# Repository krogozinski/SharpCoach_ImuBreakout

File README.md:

# SharpCoach IMU Breakout
A simple breakout board for the ST LSM6DS33 IMU using a modified Digilent Type 2A PMOD interface. The board breaks out both interrupt pins to facilitate notifying the controlling device of IMU events.

# Pinout
1. SS
2. MOSI
3. MISO
4. SCK
5. GND
6. VCC
7. INT1
8. NC
9. INT2
10. NC
11. GND
12. VCC

# License

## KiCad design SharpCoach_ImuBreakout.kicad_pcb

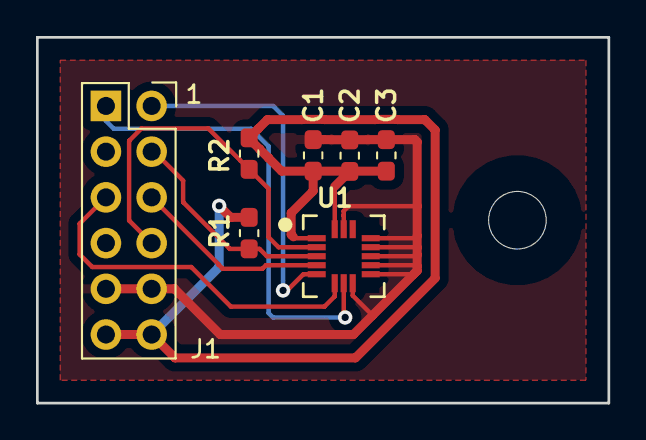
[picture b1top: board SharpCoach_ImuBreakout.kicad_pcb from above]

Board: 2 copper layers, 31.8 x 20.3 mm, 7 parts (0 on the bottom side), 8 nets.

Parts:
C1, C2: 100n; C_0603_1608Metric_Pad1.05x0.95mm_HandSolder
C3: 1u; C_0603_1608Metric_Pad1.05x0.95mm_HandSolder
J1: PMOD_Type2A_Variant01; PMOD_SpecB
R1, R2: 10k; R_0603_1608Metric_Pad1.05x0.95mm_HandSolder
U1: LSM6DS33

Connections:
+3V3: C1.1, C2.1, C3.1, J1.6, J1.12, R1.1, R2.1, U1.1, U1.16
/INT1: J1.7, U1.7
/INT2: J1.9, U1.6
/MISO: J1.3, U1.4
/MOSI: J1.2, R1.2, U1.3
/SCK: J1.4, R2.2, U1.2
/SS: J1.1, U1.5
GND: C1.2, C2.2, C3.2, J1.5, J1.11, U1.8, U1.9, U1.10, U1.11, U1.12, U1.13, U1.15

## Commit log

2018-08-01 Initial commit of schematics
2018-08-01 Started PCB layout.
2018-08-01 Started PCB trace routing
2018-08-02 Finished PCB trace routing.
2018-08-02 Added copper pour and board outline to PCB layout.
2018-08-02 Updated mask expansion to Oshpark recommended value of 2mil
2018-08-03 Added title block info to schematic and board layout. Added design info to board silkscreen.
2018-08-05 Updated silkscreen layer for inertial sensor components.
2018-08-28 Updated silkscreen with pinout
2020-05-13 Updated library paths to use submodules.
2020-10-22 Updated symbol and footprint libraries to use submodules

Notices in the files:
README.md:
License:
[License: CC BY-SA 4.0](https://creativecommons.org/licenses/by-sa/4.0/)
SharpCoach_ImuBreakout.kicad_pcb:
2019 CC BY-SA 4.0
